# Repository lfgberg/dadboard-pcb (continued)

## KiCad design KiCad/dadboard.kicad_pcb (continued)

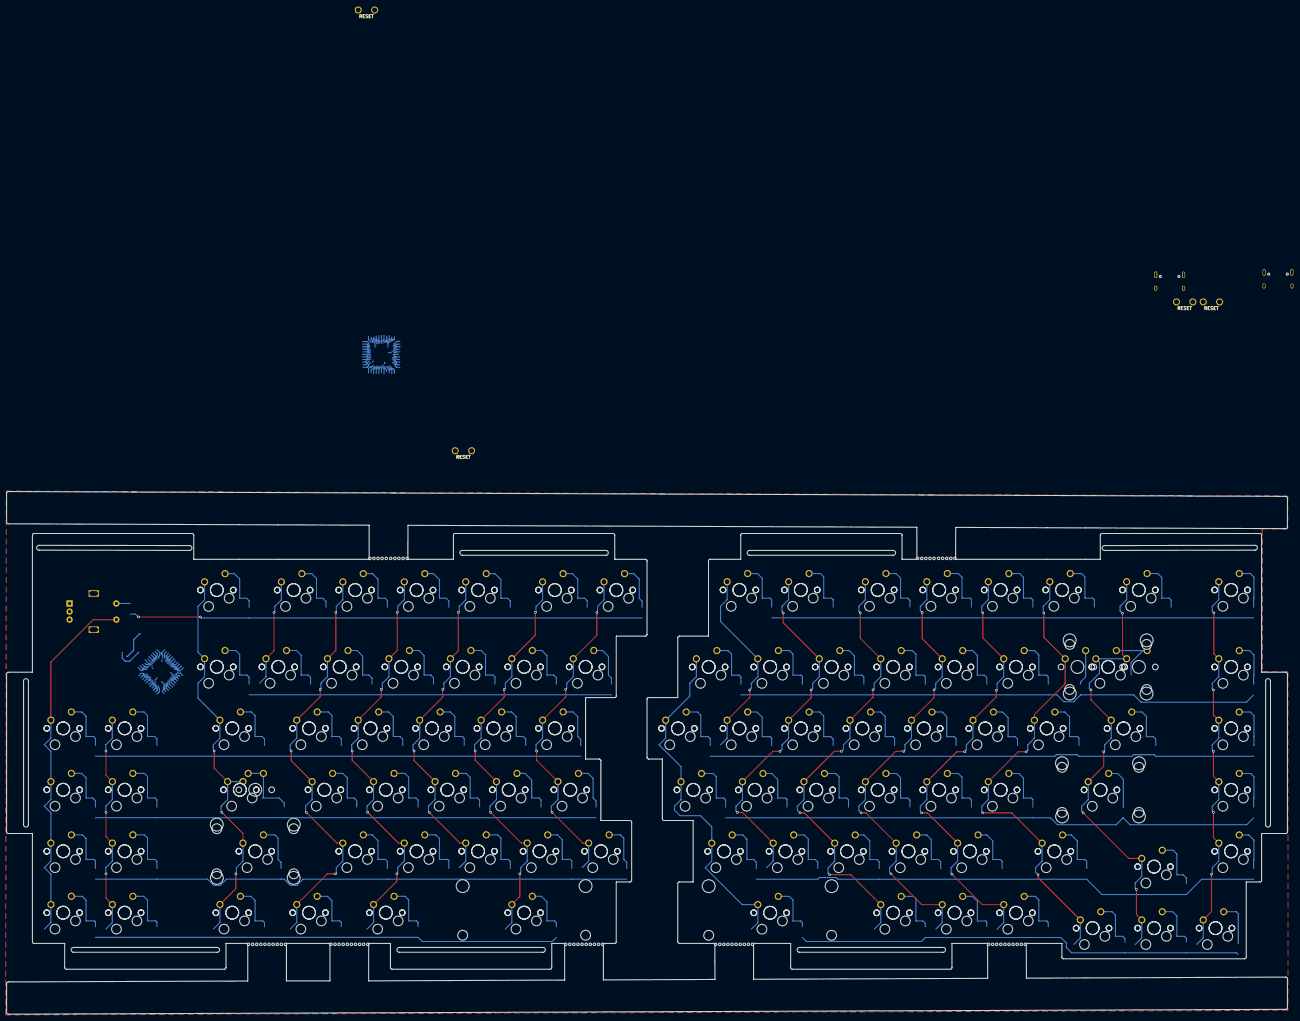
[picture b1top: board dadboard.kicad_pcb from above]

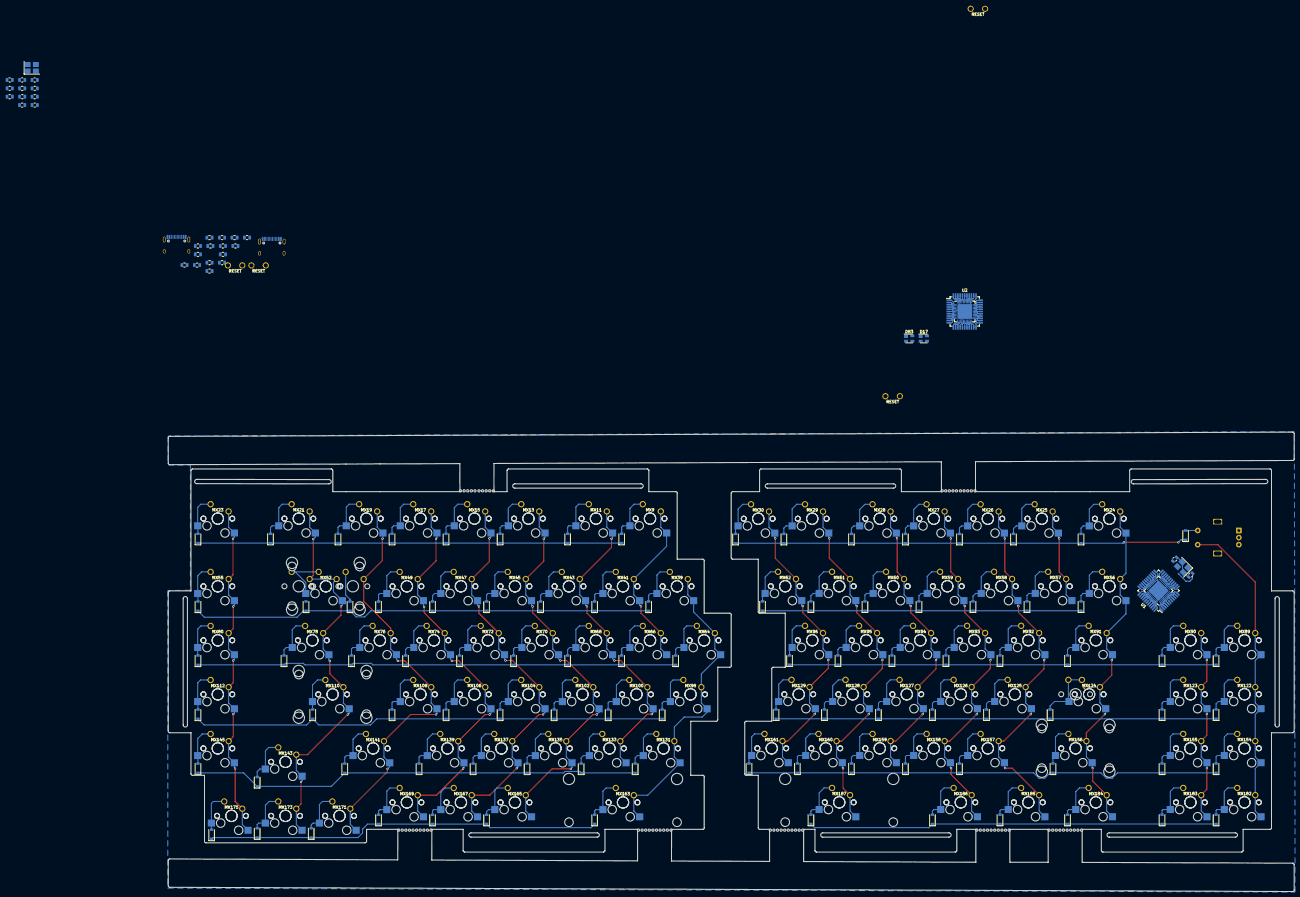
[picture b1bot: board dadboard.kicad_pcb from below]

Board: 2 copper layers, 397.0 x 162.0 mm, 322 parts (130 on the bottom side), 150 nets.

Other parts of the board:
JP1#2, JP2#2: Jumper; ResetJumper
MX43#2: 9; MXOnly-1U-Hotswap
MX44#2: Delete; MXOnly-1U-NoLED

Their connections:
CR7: MX44#2.1 (COL); also elsewhere on the board
unnamed 57: MX44#2.2 (ROW); also elsewhere on the board

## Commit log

2021-09-03 Finished matrix
2021-09-12 Routed left side
    - routed the left side of the pcb
    - revised edge cuts
    - added ports
    - added lg branding
2021-10-14 finish v1
2021-10-14 add bom
2023-02-16 add buymeacoffee
